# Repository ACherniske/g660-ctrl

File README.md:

# g660-ctrl

Firmware and support tooling for a Yamaha Grizzly 660 differential control
system.

The project is structured so one firmware tree can run in multiple roles:

- **Central module** (steering-wheel/button controller)
- **Differential module** (front or rear actuator controller)

At boot, a hardware select pin chooses which role entrypoint is launched.

---

## 1) System overview

The system controls front and rear differential actuators with three target
modes:

- `neutral`
- `limited_slip`
- `locked`

### Central module responsibilities

- Reads preset buttons (up to 6)
- Sends `set_mode` commands to front/rear diff modules
- Tracks module liveness via heartbeats
- Tracks state/fault telemetry from diff modules
- Optionally renders status on a 16x2 I2C LCD

### Differential module responsibilities

- Resolves current actuator position from 3 position sensors
- Accepts mode commands from central (and optional local selector)
- Drives motor CW/CCW until target mode is reached
- Applies timeout and invalid-sensor safety behavior
- Responds with ACK, mode status, node state, and fault status

---

## 2) Repository layout

```text
firmware/
	boot.py                     # Role-select boot entrypoint
	common/                     # Shared protocol, constants, mode definitions, inputs
	central_module/             # Central controller app + config
	diff_module/                # Differential controller app + motor/transition logic
	tools/comms_profile_validation.py
```

Key files:

- `firmware/boot.py`
- `firmware/common/constants.py`
- `firmware/common/protocol.py`
- `firmware/central_module/main.py`
- `firmware/central_module/config.py`
- `firmware/central_module/pins.py`
- `firmware/diff_module/main.py`
- `firmware/diff_module/pins.py`

---

## 3) Role and node selection

## Boot role select (central vs diff)

`firmware/boot.py` reads the boot-select GPIO and launches one module:

- `central_module.main`
- `diff_module.main`

Behavior is configured in `firmware/common/constants.py`:

- `BOOT_SELECT_PIN`
- `BOOT_SELECT_PULL`
- `BOOT_HIGH_IS_CENTRAL`

## Diff node select (front vs rear)

`diff_module.main` reads a second select pin at startup to pick node ID:

- `NODE_ID_DIFF_FRONT` (`0x11`)
- `NODE_ID_DIFF_REAR` (`0x12`)

Configured in `firmware/diff_module/pins.py`:

- `NODE_SELECT_PIN`
- `NODE_SELECT_PULL`
- `NODE_SELECT_HIGH_IS_FRONT`

This allows one diff firmware image to run as either front or rear via
hardware strapping.

---

## 4) Communications

UART is framed with a small binary protocol in
`firmware/common/protocol.py`:

Frame format:

```text
[SOF][DST][SRC][CMD][LEN][PAYLOAD...][CRC]
```

- `SOF` from `FRAME_SOF` (default `0xA5`)
- `CRC` is XOR of bytes from `DST` through payload

Important command IDs (in `firmware/common/constants.py`):

- `CMD_SET_MODE`
- `CMD_HEARTBEAT`
- `CMD_MODE_STATUS`
- `CMD_ACK`
- `CMD_STATUS_REQUEST`
- `CMD_NODE_STATE`
- `CMD_FAULT_STATUS`

Node IDs:

- Central: `0x01`
- Front diff: `0x11`
- Rear diff: `0x12`
- Broadcast: `0xFF`

---

## 5) Configuration points

## Central configuration

Edit:

- `firmware/central_module/pins.py` for GPIO and bus wiring
- `firmware/central_module/config.py` for behavior/timing

Examples:

- `BUTTON_PRESETS`
- `SET_MODE_ACK_TIMEOUT_MS`
- `SET_MODE_MAX_RETRIES`
- `HEARTBEAT_STAGGER_MS`
- `DISPLAY_ENABLED`

## Diff configuration

Edit:

- `firmware/diff_module/pins.py`

Examples:

- Motor pins (`MOTOR_CW_PIN`, `MOTOR_CCW_PIN`)
- Position sensor pins
- Optional local selector pins
- Watchdog settings
- UART pins/baudrate

---

## 6) Deployment

The project is plain MicroPython source. Typical deployment is copying the
`firmware/` contents to each controller board filesystem.

## Prerequisites

- MicroPython-compatible controller boards (ESP32-class expected)
- USB access to each board
- A file transfer tool (for example, `mpremote`, `rshell`, Thonny, etc.)
- Correct board wiring for your selected pin configuration

## A. Flash MicroPython (one-time per board)

1. Erase/flash board with a matching MicroPython firmware image.
2. Confirm REPL access over serial.

## B. Copy project files to board

Copy the `firmware/` directory contents so the board filesystem includes:

- `boot.py`
- `common/`
- `central_module/`
- `diff_module/`

`boot.py` must live at device root so it runs at startup.

## C. Configure board role by hardware

Set the boot-select strap/pin to choose:

- central role, or
- diff role

No source change is required when `BOOT_SELECT_*` wiring and constants match.

## D. Configure diff front/rear identity

On diff boards, set node-select strap/pin to choose front vs rear.

## E. Reboot and verify

1. Power cycle/reboot all modules.
2. Verify central sees both diff nodes online.
3. Press preset buttons and verify actuator movement + telemetry.
4. If enabled, verify LCD status transitions.

---

## 7) Operational notes

- Central only sends mode commands to online nodes (with startup grace window).
- `set_mode` includes retry/ACK tracking with sequence support.
- Diff modules dedupe repeated `set_mode` commands in a short window.
- Sensor invalid combinations and travel timeout stop motor and report faults.
- Optional heartbeat watchdog can reboot diff nodes on comms loss.
- Reboot loop protection can force degraded mode until stable recovery heartbeats.

---

## 8) Optional timing sanity check tool

`firmware/tools/comms_profile_validation.py` provides a lightweight check for
heartbeat stagger and reply-slot separation using current config defaults.

---

## 9) Development workflow

1. Update configuration files for your harness/wiring.
2. Deploy to bench hardware.
3. Validate sensor transitions in all 3 modes.
4. Validate heartbeat/fault behavior with central connected and disconnected.
5. Freeze known-good pin and timing values before field testing.

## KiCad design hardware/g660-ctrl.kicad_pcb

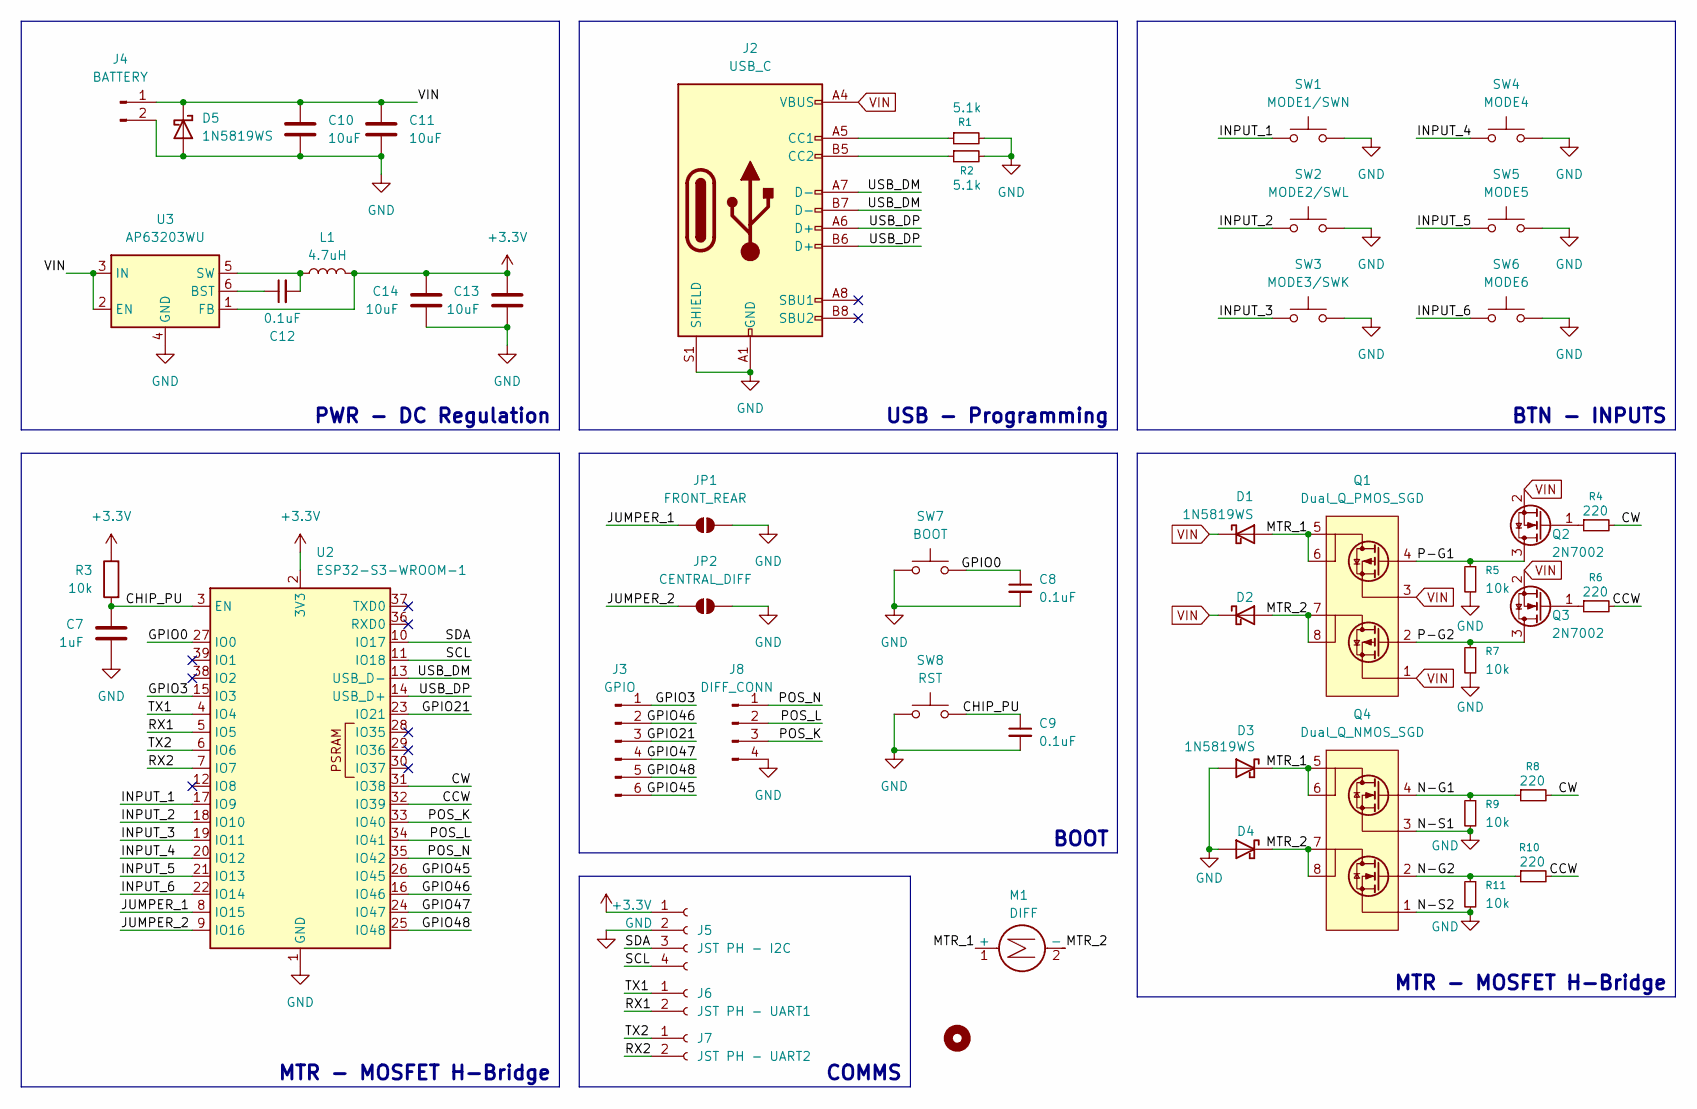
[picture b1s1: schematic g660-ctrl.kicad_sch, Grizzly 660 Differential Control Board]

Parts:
C7: 1uF; C_0805_2012Metric_Pad1.18x1.45mm_HandSolder
C8, C9, C12: 0.1uF; C_0805_2012Metric_Pad1.18x1.45mm_HandSolder
C10, C11, C13, C14: 10uF; C_0805_2012Metric_Pad1.18x1.45mm_HandSolder
D1, D2, D3, D4, D5: 1N5819WS; D_SOD-323_HandSoldering
H1: MountingHole; MountingHole_2.1mm
J2: USB_C; USB_C_Receptacle_G-Switch_GT-USB-7010ASV
J3: GPIO; GPIO_Breakout
J4: BATTERY; Battery Connection
J5: JST PH - I2C; Diff_Conn
J6: JST PH - UART1; UART
J7: JST PH - UART2; UART
J8: DIFF_CONN; Diff_Conn
JP1: FRONT_REAR; SolderJumper-2_P1.3mm_Open_TrianglePad1.0x1.5mm
JP2: CENTRAL_DIFF; SolderJumper-2_P1.3mm_Open_TrianglePad1.0x1.5mm
L1: 4.7uH; L_Bourns-SRN4018
M1: DIFF; Battery Connection
Q1: Dual_Q_PMOS_SGD; SOIC-8-1EP_3.9x4.9mm_P1.27mm_EP2.29x3mm_ThermalVias
Q2, Q3: 2N7002; SOT-23
Q4: Dual_Q_NMOS_SGD; SOIC-8-1EP_3.9x4.9mm_P1.27mm_EP2.29x3mm_ThermalVias
R1, R2: 5.1k; R_0805_2012Metric_Pad1.20x1.40mm_HandSolder
R3, R5, R7, R9, R11: 10k; R_0805_2012Metric_Pad1.20x1.40mm_HandSolder
R4, R6, R8, R10: 220; R_0805_2012Metric_Pad1.20x1.40mm_HandSolder
SW1: MODE1/SWN; Wuerth_434133025816_And_Pads
SW2: MODE2/SWL; Wuerth_434133025816_And_Pads
SW3: MODE3/SWK; Wuerth_434133025816_And_Pads
SW4: MODE4; ButtonPads
SW5: MODE5; ButtonPads
SW6: MODE6; ButtonPads
SW7: BOOT; SW_Push_1P1T_NO_Vertical_Wuerth_434133025816
SW8: RST; SW_Push_1P1T_NO_Vertical_Wuerth_434133025816
U2: ESP32-S3-WROOM-1
U3: AP63203WU; TSOT-23-6

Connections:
+3.3V: C13.1, C14.1, J5.1, L1.2, R3.1, U2.2 (3V3), U3.1 (FB); also elsewhere on the board
/CCW: R6.2, R10.2, U2.32 (IO39)
/CHIP_PU: C7.1, C9.1, R3.2, SW8.2, U2.3 (EN); also elsewhere on the board
/CW: R4.2, R8.2, U2.31 (IO38)
/GPIO0: C8.1, SW7.2, U2.27 (IO0); also elsewhere on the board
/GPIO3: J3.1, U2.15 (IO3)
/GPIO21: J3.3, U2.23 (IO21)
/GPIO45: J3.6, U2.26 (IO45)
/GPIO46: J3.2, U2.16 (IO46)
/GPIO47: J3.4, U2.24 (IO47)
/GPIO48: J3.5, U2.25 (IO48)
/INPUT_1: SW1.1, U2.17 (IO9)
/INPUT_2: SW2.1, U2.18 (IO10)
/INPUT_3: SW3.1, U2.19 (IO11)
/INPUT_4: SW4.1, U2.20 (IO12)
/INPUT_5: SW5.1, U2.21 (IO13)
/INPUT_6: SW6.1, U2.22 (IO14)
/JUMPER_1: JP1.1 (A), U2.8 (IO15)
/JUMPER_2: JP2.1 (A), U2.9 (IO16)
/MTR_1: D1.2 (A), D3.1 (K), M1.1 (+), Q1.5 (D), Q1.6 (D), Q4.5 (D), Q4.6 (D)
/MTR_2: D2.2 (A), D4.1 (K), M1.2 (-), Q1.7 (D), Q1.8 (D), Q4.7 (D), Q4.8 (D)
/N-G1: Q4.4 (G), R8.1, R9.1
/N-G2: Q4.2 (G), R10.1, R11.1
/P-G1: Q1.4 (G), Q2.3 (D), R5.1
/P-G2: Q1.2 (G), Q3.3 (D), R7.1
/POS_K: J8.3, U2.33 (IO40); also elsewhere on the board
/POS_L: J8.2, U2.34 (IO41); also elsewhere on the board
/POS_N: J8.1, U2.35 (IO42); also elsewhere on the board
/RX1: J6.2, U2.5 (IO5); also elsewhere on the board
/RX2: J7.2, U2.7 (IO7)
/SCL: J5.4, U2.11 (IO18); also elsewhere on the board
/SDA: J5.3, U2.10 (IO17); also elsewhere on the board
/TX1: J6.1, U2.4 (IO4); also elsewhere on the board
/TX2: J7.1, U2.6 (IO6)
/USB_DM: J2.A7 (D-), J2.B7 (D-), U2.13 (USB_D-)
/USB_DP: J2.A6 (D+), J2.B6 (D+), U2.14 (USB_D+)
GND: C7.2, C8.2, C9.2, C10.2, C11.2, C13.2, C14.2, D3.2 (A), D4.2 (A), D5.2 (A), J2.A1 (GND), J2.A12 (GND), J2.B1 (GND), J2.B12 (GND), J2.S1 (SHIELD), J4.2, J5.2, J8.4, JP1.2 (B), JP2.2 (B), Q4.1 (S), Q4.3 (S), R1.2, R2.2, R5.2, R7.2, R9.2, R11.2, SW1.2, SW2.2, SW3.2, SW4.2, SW5.2, SW6.2, SW7.1, SW8.1, U2.1 (GND), U2.40 (GND), U2.41 (GND), U3.4 (GND); also elsewhere on the board
unnamed: J2.A5 (CC1), R1.1
unnamed: J2.B5 (CC2), R2.1
unnamed: Q2.1 (G), R4.1
unnamed: Q3.1 (G), R6.1
unnamed: C12.1, U3.6 (BST)
unnamed: C12.2, L1.1, U3.5 (SW)
VIN: C10.1, C11.1, D1.1 (K), D2.1 (K), D5.1 (K), J2.A4 (VBUS), J2.A9 (VBUS), J2.B4 (VBUS), J2.B9 (VBUS), J4.1, Q1.1 (S), Q1.3 (S), Q2.2 (S), Q3.2 (S), U3.2 (EN), U3.3 (IN)

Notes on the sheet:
USB - Programming
PWR - DC Regulation
BTN - INPUTS
BOOT
COMMS
MTR - MOSFET H-Bridge

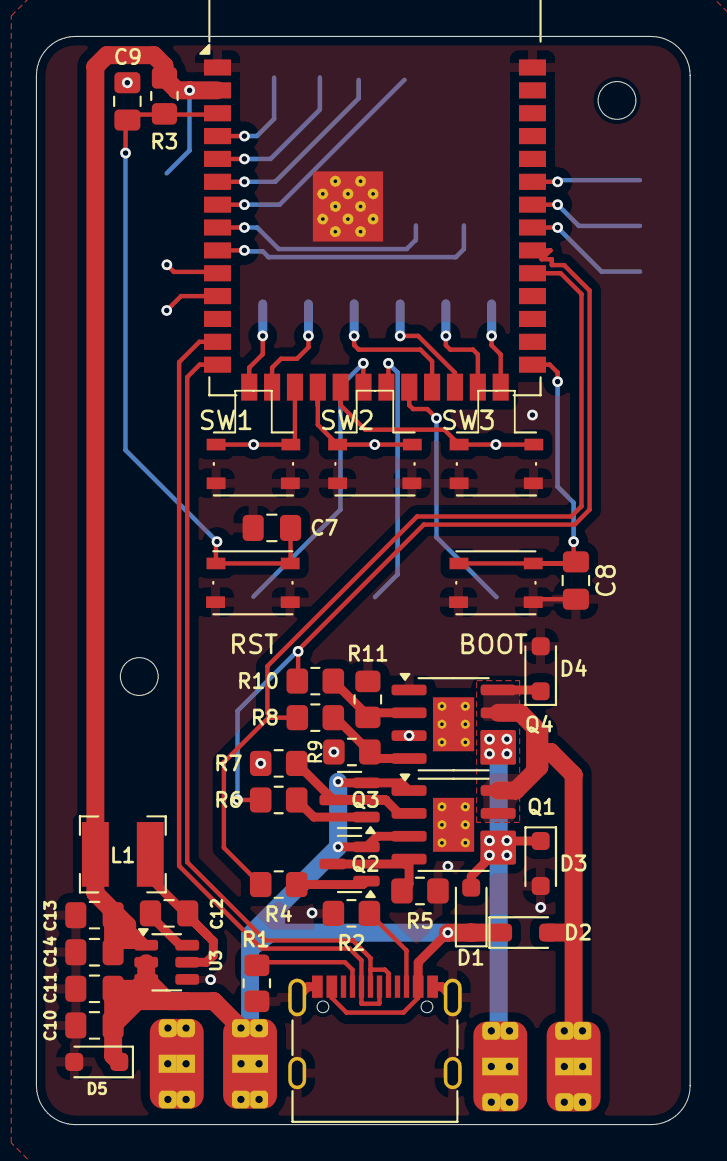
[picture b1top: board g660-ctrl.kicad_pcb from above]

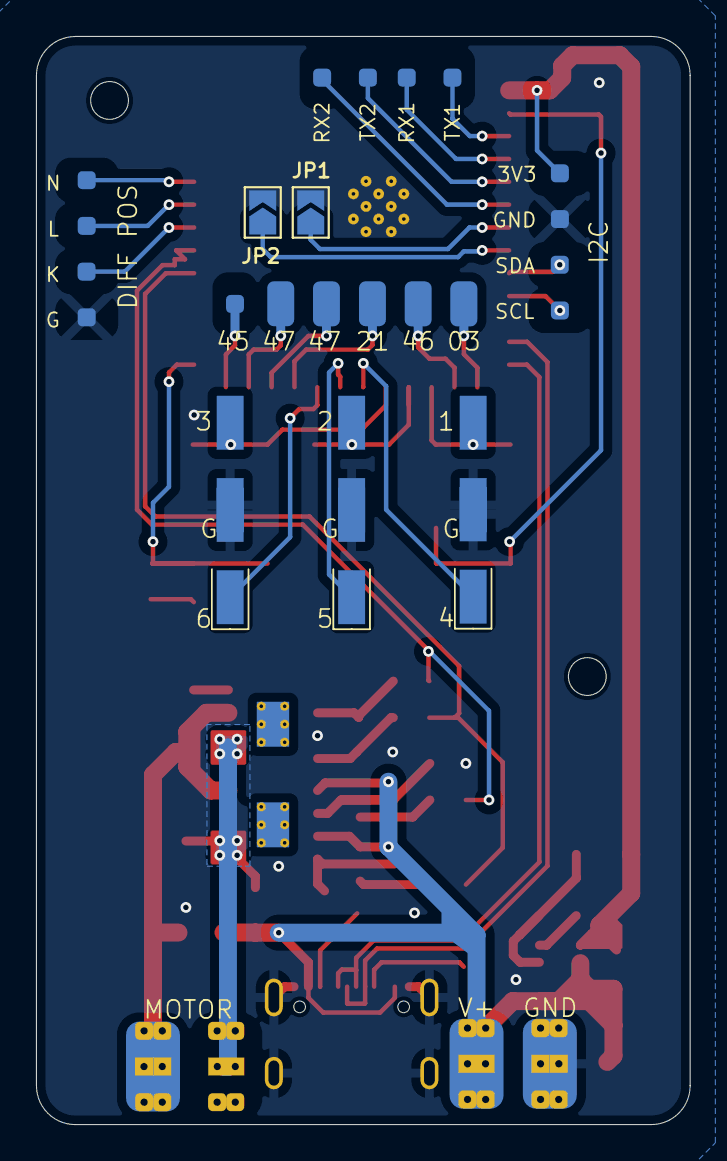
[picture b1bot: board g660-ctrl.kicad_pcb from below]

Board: 4 copper layers, 36.3 x 60.5 mm, 51 parts (6 on the bottom side), 44 nets.

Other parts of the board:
BOOT: BOOT; SW_Push_1P1T_NO_Vertical_Wuerth_434133025816
DIFF POS: DIFF_CONN; Diff_Conn
H1#2: MountingHole; MountingHole_2.1mm
I2C: JST PH - I2C; Diff_Conn
RST: RST; SW_Push_1P1T_NO_Vertical_Wuerth_434133025816
TX1: JST PH - UART1; UART

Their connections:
+3.3V: I2C.1; also elsewhere on the board
/CHIP_PU: RST.2; also elsewhere on the board
/GPIO0: BOOT.2; also elsewhere on the board
/POS_K: DIFF POS.3; also elsewhere on the board
/POS_L: DIFF POS.2; also elsewhere on the board
/POS_N: DIFF POS.1; also elsewhere on the board
/RX1: TX1.2; also elsewhere on the board
/SCL: I2C.4; also elsewhere on the board
/SDA: I2C.3; also elsewhere on the board
/TX1: TX1.1; also elsewhere on the board
GND: BOOT.1, DIFF POS.4, I2C.2, RST.1; also elsewhere on the board

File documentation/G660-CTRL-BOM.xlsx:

G660 CTRL — Bill of Materials
Qty | Designator | Val | Footprint | Link
25 | C8,C9,C12 | 0.1uf | Capacitor_SMD:C_0805_2012Metric_Pad1.18x1.45mm_HandSolder | maker e
10 | C7 | 1uf | Capacitor_SMD:C_0805_2012Metric_Pad1.18x1.45mm_HandSolder | maker e
30 | C10,C11,C13,C14 | 10uf | Capacitor_SMD:C_0805_2012Metric_Pad1.18x1.45mm_HandSolder | maker e
35 | D1,D2,D3,D4,D5 | 1n5819ws | Diode_SMD:D_SOD-323_HandSoldering | https://www.mouser.com/ProductDetail/Diodes-Incorporated/1N5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
10 | J2 |  | Connector_USB:USB_C_Receptacle_G-Switch_GT-USB-7010ASV | https://www.mouser.com/ProductDetail/Amphenol-Commercial-Pro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
10 | L1 | 4.7uh | Inductor_SMD:L_Bourns-SRN4018 | https://www.mouser.com/ProductDetail/Bourns/SRN4018BTA-4R7M?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
10 | Q1 |  | Package_SO:SOIC-8-1EP_3.9x4.9mm_P1.27mm_EP2.29x3mm_ThermalVias | https://www.mouser.com/ProductDetail/onsemi/FDS4935A?qs=FOlm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
10 | Q4 |  | Package_SO:SOIC-8-1EP_3.9x4.9mm_P1.27mm_EP2.29x3mm_ThermalVias | https://www.mouser.com/ProductDetail/onsemi/FDS9926A?qs=HK%2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
20 | Q2,Q3 | 2n7002 | Package_TO_SOT_SMD:SOT-23 | https://www.mouser.com/ProductDetail/onsemi/2N7002?qs=0dwsXD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
20 | R1,R2 | 5.1k | Resistor_SMD:R_0805_2012Metric_Pad1.20x1.40mm_HandSolder | maker e 5.11k
35 | R3,R5,R7,R9,R11 | 10k | Resistor_SMD:R_0805_2012Metric_Pad1.20x1.40mm_HandSolder | maker e
30 | R4,R6,R8,R10 | 220 | Resistor_SMD:R_0805_2012Metric_Pad1.20x1.40mm_HandSolder | maker e 221
35 | SW1,SW2,SW3,SW7,SW8 |  | g660-f:Wuerth_434133025816_And_Pads | https://www.mouser.com/ProductDetail/Wurth-Elektronik/434133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
10 | U2 | ESP32-S3-WROOM-1 | RF_Module:ESP32-S3-WROOM-1 | https://www.mouser.com/ProductDetail/Espressif-Systems/ESP32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
10 | U3 | ap63203wu | Package_TO_SOT_SMD:TSOT-23-6 | https://www.mouser.com/ProductDetail/Diodes-Incorporated/AP6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
10 | Q4 | PMOS IRF9510PBF |  | https://www.mouser.com/ProductDetail/Vishay-Semiconductors/I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

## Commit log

2026-03-29 feat: Initialize KiCad project
2026-03-29 feat: Implement G_CW logic
2026-03-29 style: Clean up schematic and reassign designators
2026-03-29 feat: Add SW_N inverter circuit
2026-03-31 feat: Implement CCW logic
2026-04-04 docs: Update readme to reflect the pivot in project scope
2026-04-04 feat: Add DifferentialMode class with drive mode definitions and helpers
2026-04-04 feat: Implement Switch and SwitchManager classes for debounced switch input handling
2026-04-04 feat: Add DriveModeSelector and DifferentialPositionSensors for mode selection handling
2026-04-04 feat: Implement MotorController class for differential motor control
2026-04-04 feat: Add hardware abstraction layer for differential controller boards
2026-04-04 feat: Add pin definitions for differential module configuration
2026-04-04 feat: Add main control loop for differential module
2026-04-05 fix: GPIO 34 is an input only and does not have the capability for internal pull up. Switch to GPIO 13
2026-04-05 feat: Add boot module with entry into central or diff modules based on jumper
2026-04-05 feat: Add constants and protocol for UART communication and mode commands
2026-04-05 feat: Implement hardware abstraction layer and differential mode definitions
2026-04-05 chore: Move previous implementation testing to old folder. !TODO: remove later
2026-04-05 style: Update code to PEP8
2026-04-05 refactor: Move modes and switch input to common package
2026-04-05 feat: Complete diff_module implementation
2026-04-05 feat: Add central module implementation with button presets and UART communication
2026-04-05 refactor: Remove old central and differential module implementations
2026-04-05 feat: Implement optional I2C LCD display support with configuration and status update
2026-04-05 feat: Add offline warning display for front and rear differential modules
2026-04-05 feat: Implement heartbeat watchdog for central communication loss detection
2026-04-05 feat: Add central control enable configuration to allow operating diffs in standalone mode
2026-04-05 style: Fix indentation in diff module pin configuration
2026-04-05 feat: Implement command blocking indication for offline differential nodes
2026-04-05 feat: Add configuration validation to ensure proper deployment settings
2026-04-05 feat: Enhance command reliability with startup grace period and acknowledgment handling
2026-04-05 feat: Add shared-bus contention mitigation and heartbeat handling improvements
2026-04-05 feat: Implement watchdog reboot-loop protection and configuration validation
2026-04-05 fix: keep heartbeat watchdog active on sensor fault path
2026-04-05 feat: harden central-diff comms telemetry and recovery
2026-04-05 fix: add InputModeResolver class for active switch mode resolution
2026-04-05 docs: update README.md with detailed system overview and configuration instructions
2026-04-16 feat: Complete V1 PCB
2026-04-30 feat: Complete G660 control board
